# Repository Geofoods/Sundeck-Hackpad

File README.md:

# Sundeck-Hackpad

Hackpad that I made with specific things to match my preferences.

## Features
- 5 keys
  - Play/Pause button
  - Open Spotify
  - Take a Screenshot
  - Open New Tab
  - Switch Windows
- Two Mini LEDs
- Rotary Encoder Switch that controls volume and mutes/unmutes
- KMK firmware
- Stands itself up for more ergonomic use

## PCB

Here is a picture of my schematic made in KiCad. There are six customizable buttons.

<table>
  <tr>
    <th>Schematic</th>
    <th>PCB</th>
  </tr>
  <tr>
    <td>
      
    </td>
    <td>
      
    </td>
  </tr>
</table>

## CAD Model

Here is the CAD made in Fusion 360. It should all fit together with 4x M3x5mx4mm heatset inserts and 4x M3x16mm screws.

## Why I made the Hackpad

I thought that this project was pretty fun and was actually my first attempt at doing these kind of things (KiCAD, Fusion 360). It's a nice beginner project that is accessible, and I made it into my own with it's own custom properties

## BOM

- 1x Seeed XIAO RP2040
- 2x SK6812 MINI-E LEDs
- 4x M3x16mm screws
- 1x Case (2 3D printed parts)
- 5x Blank DSA keycaps (White)
- 5x MX-Style switches
- 1x EC11 Rotary encoders
- 4x M3x5mx4mm heatset inserts

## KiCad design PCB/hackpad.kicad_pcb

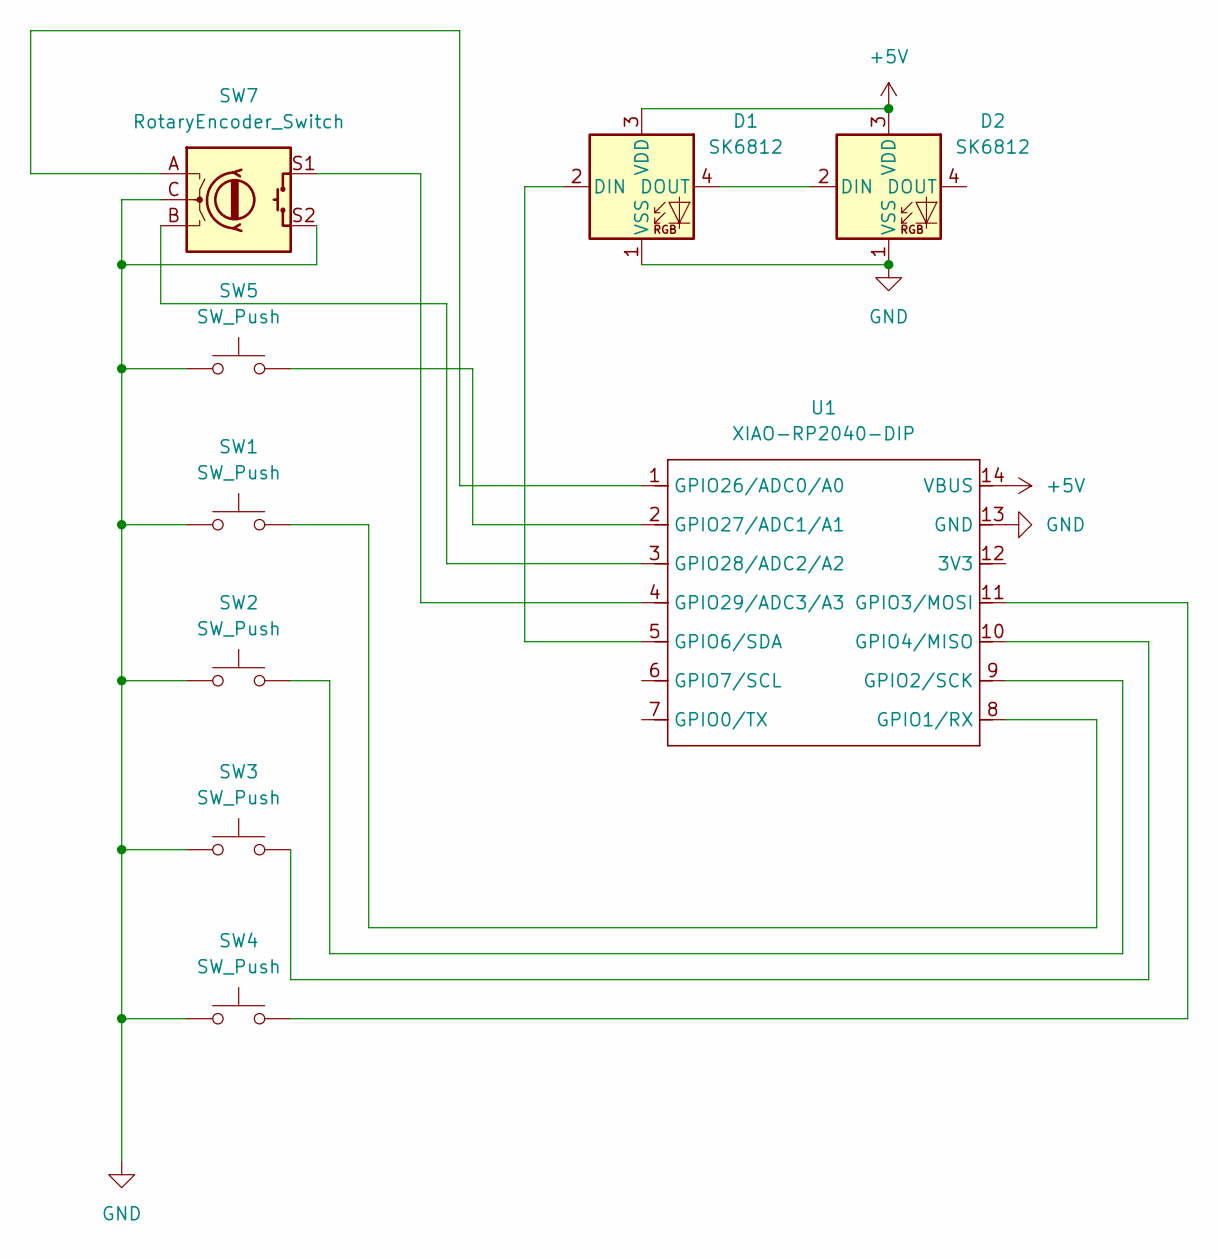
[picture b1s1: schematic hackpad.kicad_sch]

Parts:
D1, D2: SK6812; LED_SK6812MINI_PLCC4_3.5x3.5mm_P1.75mm
SW1, SW2, SW3, SW4, SW5: SW_Push; SW_Cherry_MX_1.00u_PCB
SW7: RotaryEncoder_Switch; RotaryEncoder_Alps_EC11E-Switch_Vertical_H20mm
U1: XIAO-RP2040-DIP

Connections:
+5V: D1.3 (VDD), D2.3 (VDD), U1.14 (VBUS)
GND: D1.1 (VSS), D2.1 (VSS), SW1.1, SW2.1, SW3.1, SW4.1, SW5.1, SW7.C, SW7.S2, U1.13 (GND)
unnamed: D1.2 (DIN), U1.5 (GPIO6/SDA)
unnamed: D1.4 (DOUT), D2.2 (DIN)
unnamed: SW1.2, U1.8 (GPIO1/RX)
unnamed: SW2.2, U1.9 (GPIO2/SCK)
unnamed: SW4.2, U1.11 (GPIO3/MOSI)
unnamed: SW3.2, U1.10 (GPIO4/MISO)
unnamed: SW7.A, U1.1 (GPIO26/ADC0/A0)
unnamed: SW5.2, U1.2 (GPIO27/ADC1/A1)
unnamed: SW7.B, U1.3 (GPIO28/ADC2/A2)
unnamed: SW7.S1, U1.4 (GPIO29/ADC3/A3)

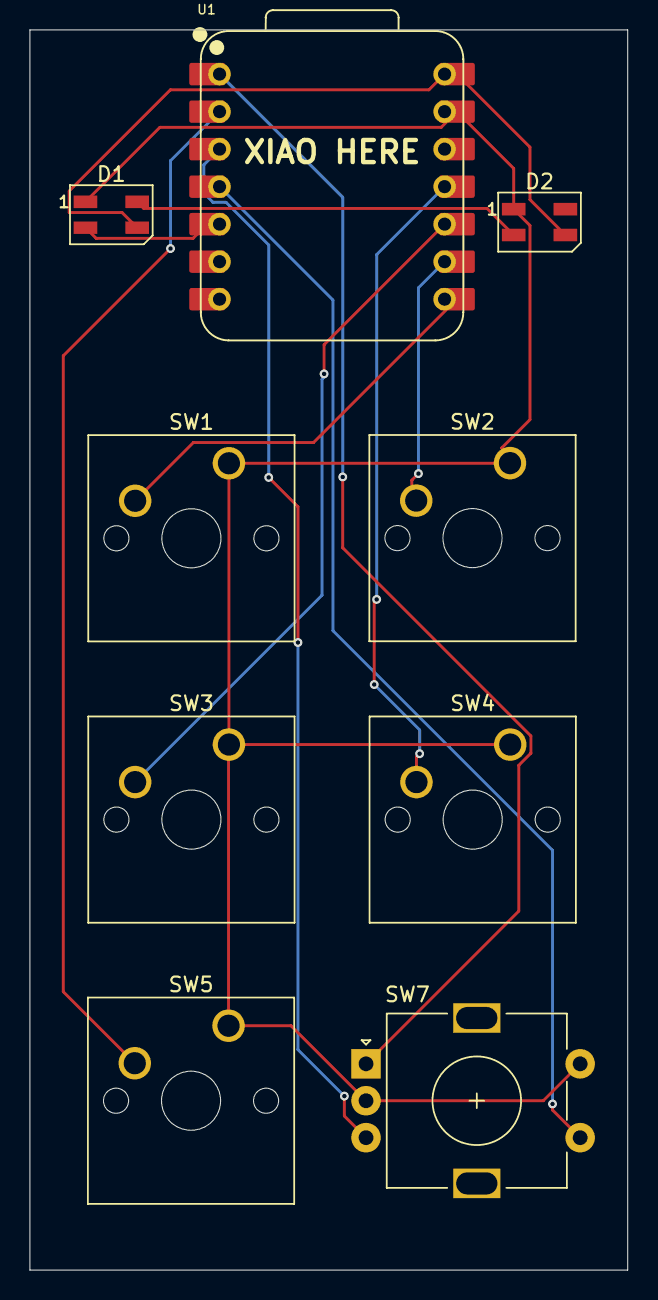
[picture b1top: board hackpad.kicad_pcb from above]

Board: 2 copper layers, 40.5 x 84.0 mm, 9 parts (0 on the bottom side), 12 nets.

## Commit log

2026-01-10 Adding Project Files
2026-01-11 Update README.md
    Expanded README with detailed features, PCB, CAD model, and BOM.
2026-01-11 Revise section headers in README.md
    Updated section headers for CAD Model and BOM in README.
2026-01-11 Refactor README features section for clarity
    Formatted the features section and improved readability.
2026-01-11 Add screenshot to README
    Added an additional screenshot to the README.
2026-01-19 Adding Feedback
2026-01-19 Adding Feedback
    Adding Feedback
2026-01-19 Revise images and update BOM in README
    Updated images and BOM details in README.
2026-01-19 Add 3d models
2026-01-20 Added BOM as CSV
2026-01-23 Add CSV
2026-01-23 Update image in README with new screenshot
2026-01-23 Add new models
2026-01-24 Revise BOM.csv to structured format with headers
    Updated the BOM format to include headers and corrected item descriptions.
2026-01-24 Add Section To Readme
2026-01-25 Changing SK6812 to SK6812 MINI LEDS
